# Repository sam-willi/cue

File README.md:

# Cue

**Speak with intention.** Cue is a discreet behind-the-ear (BTE) speech coach that gives a private haptic tap when a speaking habit (a run of fillers, rushing, no pauses, a long turn, speaking too quietly) is getting in your way, so you notice it in the moment and replace it with a pause.

This repository is the **software MVP**: a web app that listens through the microphone, detects these behaviors in real time, and shows each haptic cue on a 3D model of the device in place of the hardware. Product context, confirmed decisions, and open questions live in [`CUE_CONTEXT.md`](CUE_CONTEXT.md). Read it before proposing changes.

**Live demo:** https://cue-samanthajwilliamson-2541.vercel.app (it has no server Deepgram key, so use your own; see [Your own Deepgram key](#your-own-deepgram-key)).

> Status: prototype for validating the behavior loop. Not a medical device. Detection accuracy has not been measured on real users yet.

## How Cue decides to tap

Cue is a behavioral coach, not a filler counter ([`SOFTWARE.md`](SOFTWARE.md)). Detectors notice fillers, pace, pauses, turn length and volume; a **decision engine** (`src/lib/cue/engine.ts`) asks whether a tap would help right now. There are two modes, switched in the app or by double-tapping the device:

|                  | Conversation                              | Presentation                                                               |
| ---------------- | ----------------------------------------- | -------------------------------------------------------------------------- |
| Fillers          | 3 fillers within 12 s, or 8 per min       | um/uh above 5 per min over the last 60 s; "like"/"lowkey" count half       |
| Rushing          | 4.5 syl/s, then 20% over your own pace    | 4.0 syl/s, then 10% over your own pace                                     |
| No pause         | 30 s without a pause                      | 22 s without a ≥0.6 s pause                                                |
| Long turn        | 90 s                                      | Not live (a talk is one long turn)                                         |
| Too quiet        | 6 dB under your calibrated volume for 3 s | 6 dB under your calibrated volume for 10 s                                 |
| Gap between taps | 15 s cooldown (setting: 10–20 s)          | At least 25 s, at most 2 taps per minute; only the highest priority taps\* |

\* Presentation priority when several are due at once: rushing > no pause > filler > too quiet. The Presentation numbers are research-based starting points to test ([`CUE_CONTEXT.md`](CUE_CONTEXT.md) §26, decision 11).

- **Patterns, not single fillers.** One "um" is normal. Settings has an "every filler" testing mode (cooldown drops to 1.5 s). Whether patterns or every filler helps more is still a working assumption to test.
- **Pace against your own normal.** Rushing starts at the preset and, after your first minute of speech, becomes 20% (Conversation) or 10% (Presentation) over your own pace, never below 3.6 syl/s and never above 6 syl/s (about 250 words a minute), so a session that opens with very fast talking can't teach Cue that it is normal. A pace just over the limit has to hold for 3 s; at 1.25 times the limit or more, 1.5 s is enough.
- **Sustained behaviors wait for a natural break** (up to 3 s; 1 s for rushing, since someone racing ahead rarely leaves one) so the tap doesn't land mid-word.
- **Did it work?** 8 s after each tap Cue checks whether you paused, slowed down, stopped the fillers or spoke up, and gives more room next time if you did. Review shows "tapped: 3 in 9 s, and it worked".

## What it detects

| Behavior                              | How                                                                                                                                                                                                                                                                                                                                                                                                                                                                                                                                                                                                                                                                                                                                                                                                                                                              |
| ------------------------------------- | ---------------------------------------------------------------------------------------------------------------------------------------------------------------------------------------------------------------------------------------------------------------------------------------------------------------------------------------------------------------------------------------------------------------------------------------------------------------------------------------------------------------------------------------------------------------------------------------------------------------------------------------------------------------------------------------------------------------------------------------------------------------------------------------------------------------------------------------------------------------- |
| "um", "uh" (also "er", "erm", "ah")   | Deepgram **Flux** streaming ASR (results every ~0.2 s, keeps fillers; Nova-3 drops most fillers live). "hmm" is not counted: it's often a listening sound.                                                                                                                                                                                                                                                                                                                                                                                                                                                                                                                                                                                                                                                                                                       |
| Filler "like"                         | Rules over neighbouring words, part-of-speech tags, punctuation and pauses. "I like went to the mall" counts; "I like tofu" doesn't. Ambiguous cases never count, and every decision has a readable reason.                                                                                                                                                                                                                                                                                                                                                                                                                                                                                                                                                                                                                                                      |
| Quote "like" ("she was like, no way") | On by default, toggle in Settings                                                                                                                                                                                                                                                                                                                                                                                                                                                                                                                                                                                                                                                                                                                                                                                                                                |
| "About" "like" ("like twenty people") | Off by default, toggle in Settings                                                                                                                                                                                                                                                                                                                                                                                                                                                                                                                                                                                                                                                                                                                                                                                                                               |
| Filler "lowkey"                       | Its own classifier (`lowkeyClassifier.ts`): "it's lowkey good" counts; "keep it low-key" doesn't.                                                                                                                                                                                                                                                                                                                                                                                                                                                                                                                                                                                                                                                                                                                                                                |
| Speaking too fast                     | Syllables per second over a rolling 8 s window, pauses over 0.6 s excluded, sustained for 3 s. Thresholds above.                                                                                                                                                                                                                                                                                                                                                                                                                                                                                                                                                                                                                                                                                                                                                 |
| No pause                              | Time since your last meaningful pause. A pause is a gap of 0.6 s or more between your words, or the same length of real silence in the mic audio (Silero voice detection, `src/lib/audio/voiceDetector.ts`): word timings from the transcript drift, so either counts. If the voice detector can't load, word timing is used alone.                                                                                                                                                                                                                                                                                                                                                                                                                                                                                                                              |
| Long turn                             | How long your current speaking turn has run ("give the other person space"). Conversation only.                                                                                                                                                                                                                                                                                                                                                                                                                                                                                                                                                                                                                                                                                                                                                                  |
| Speaking too quietly (calibrated)     | You set the target with a short read-aloud (**Set my volume**) for each mode, saved on this device only as one loudness number per mode (no audio). Mic level is K-weighted (the ITU-R BS.1770 filter, so low rumble doesn't count) and measured only while you're actually voicing a word: inside a word's time span from the transcript, and where the voice detector heard a voice (the "active speech level" idea from ITU-T P.56). It is and adjusted for room noise (0.6 dB per dB of noise change, capped at ±10 dB). Without a calibration for the current mode, too-quiet cues are off and the app asks you to set it. A **Volume feedback** switch per mode turns volume coaching off entirely, so you never have to set a volume for that mode (saved on this device). Gain control and noise suppression are off so the measurement isn't distorted. |

"um"/"uh" are detected on the first confident result (confidence ≥ 0.8), and a clear filler "like" as soon as the next word is heard; ambiguous cases wait for more words. Detection is not the same as a tap: taps follow the pattern rules above. Each cue's measured delay appears in the app.

### Three cues

Live, Cue only ever asks for three things (decision 18). Every cue starts with a sharp onset (`src/lib/cue/patterns.ts`).

| Cue       | Haptic                                         | When                                                        |
| --------- | ---------------------------------------------- | ----------------------------------------------------------- |
| Pause     | One tap (50 ms)                                | No pause for a while, a long turn, or a run of filler words |
| Slow down | Slow steps (three 100 ms pulses, 250 ms apart) | Rushing                                                     |
| Speak up  | Long push (450 ms)                             | Too quiet                                                   |

On screen, each cue appears as a large card right under the controls, in its color (pause red, slow down orange, speak up green, matching the report), with what to do and why. It stays six seconds, long enough to glance down and read, and every cue so far is listed under it with the time it came. The 3D device at the bottom of the page still draws each cue as rings leaving the motor; a faint gray ring there means "noticed, not a pattern yet", a testing aid.

**Your own filler words.** In Settings you can add up to 20 words or short phrases you lean on ("so", "basically", "you know"). Cue counts one every time it's said (there's no check of how it was used, unlike "like"), and they feed the same pattern rules as the built-in fillers. The list is saved on this device. The list is also sent to Deepgram as "keyterms", words to listen for specially, so they are transcribed more reliably.

### Session report

When a session ends, the app builds a report (decision 19, `src/lib/cue/report.ts`, drawn by `src/app/ReportView.tsx`): a **Speak score**, directly under it **what to do differently next time**, then one card per area.

**Next time, do this.** Up to three actions, the one that cost the most points first. Each is an action in a few words ("Slow down"), how in one sentence ("Finish the last word of each sentence, breathe in, then begin the next one"), and the finding behind it ("Pace: you were rushing 23% of the time"). The full technique with its drill is on that area's card.

**Speak score (decision 25).** One number out of 100 with a level (Very low, Low, OK, High, Very high), built from points per area the way a sleep score is: pace 30, pauses 25, filler words 25, volume 10, pitch 10. Each area earns points on a sliding scale, not pass or fail. An area that couldn't be measured (no microphone, no volume set) is left out and the rest are scaled to 100. Fillers at or under two a minute earn full points, so it is not a test of saying none. It needs about 30 seconds of talking. Reading from notes and wording are not scored.

**Graphics.** Pace is a line over the comfortable range with any rushing picked out; pauses are a strip of the session where each bar is a stretch of talking and each gap a pause; pitch is a contour around your typical pitch; fillers are bars; volume and reading from notes are meters with the line worth working on marked. **Color (decision 26).** Each scored area has its own vivid color wherever it appears (its ring segment, icon, chart and technique), in rainbow order round the ring: pauses red, pace orange, volume green, filler words blue, pitch violet. Colors are used at full strength on gray, with no pale washes. Color says which area, never good or bad. The part worth working on is drawn in ink, so it stands apart from every hue for any kind of color vision. The colors are tokens in `globals.css` (`--area-*`), with brighter steps for dark mode. Each area has a **technique** (decision 24): one physical action plus a drill, such as "Land the last word" for rushing. Its one-sentence form is what "Next time, do this" shows; the full version with the drill is on every card, open where the area needs work and one press away otherwise, so it can be read even when a session flagged nothing. It appears under **Speaking insights**. The button of the same name beside Start listening opens it and scrolls to it; while a session is running the button reads "Stop and see insights" and ends the session first.

| Area               | What it reports                                                                                                                                                                                               |
| ------------------ | ------------------------------------------------------------------------------------------------------------------------------------------------------------------------------------------------------------- |
| Pauses             | How often you paused and your longest stretch without one.                                                                                                                                                    |
| Pace               | Average and fastest words per minute, the share of the session spent rushing, a chart of pace from start to finish, and what you were saying where you sped up: up to three quoted passages with their times. |
| Volume             | How much of the session you spent well below the volume you set (needs a set volume).                                                                                                                         |
| Filler words       | Fillers per minute and a count of each word, including your own. If you leaned on a common habit word that isn't on your list ("basically", "you know"), the report offers to add it.                         |
| Pitch and tone     | How much your pitch moved, from the microphone (`src/lib/cue/pitch.ts`, using the pitchy library). Under 2 semitones of spread reads as flat.                                                                 |
| Reading from notes | If you paste your notes or script, the share of your talk that matched them word for word (runs of 5+ words). Notes stay in the browser tab.                                                                  |
| Inclusive language | Terms from a list of about 570 (`src/lib/cue/inclusive.ts`), each with an alternative. Most come from retext-equality, cut down to what suits speech by `scripts/build-inclusive.mjs`.                        |

Pitch and volume need a microphone session. All of the report's thresholds are starting points that haven't been tested with users yet.

**Touch controls (simulated in the app).** The device's touch surface is for controls only: **hold 1.5 s** = Cue on/off, **double-tap** = switch Conversation / Presentation mode. A single tap or a lingering touch does nothing, so adjusting your hair or glasses won't trigger it. Confirmations are swelling or fading _ramps_ with no sharp onset, drawn as a neutral glow without rings, so they can't be mistaken for a coaching cue.

**Only the wearer is coached, by hardware.** On the device, a bone-conduction sensor confirms when you're the one speaking; the microphone (which hears everyone) feeds speech-to-text; a vibration motor behind the ear taps. Cue coaches only words the bone sensor confirms. This web prototype has no bone sensor, so it treats all speech as yours; Practice can simulate a friend cutting in.

A detection is withheld (not tapped) when confidence is too low, when it isn't a pattern yet, within the gap after the last tap, while muted, when its category is off, or when the behavior isn't live in the current mode. Withheld detections still show in the app's "Why Cue acted" log.

### Continuous learning

Cue learns each wearer across sessions and changes how it coaches them (decision 27, [`docs/continuous-learning.md`](docs/continuous-learning.md)): **observe** (a digest of numbers after each session) → **discover** (patterns that hold across sessions) → **remember** (a profile in this browser) → **adapt** (a personal coaching plan the live engine uses) → **evaluate** (taps against taps held back on purpose, strategies against each other) → **improve** (adopt what works, step back where you've improved, move your focus on).

- **Your focus** under the controls: one skill at a time, picked from your sessions or by you.
- **Cue updated** cards after a session, only when Cue learned or changed something, with "That's not right" to undo it.
- **A check-in** after each session: were the taps helpful, too many, or distracting, and what kind of session it was.
- **What Cue has learned**: your speaking patterns, your preferences, and how Cue has adapted (what it learned, what it changed), with controls to confirm, correct, pause, forget a session, or reset.
- **Learning timeline**: how you've improved, and how Cue has improved at coaching you.
- **Practice sandbox**: a separate memory for practice sentences and simulated speakers, so they never teach Cue about your real speech.

## Testing with AirPods

Until the device exists, AirPods (or any headphones with a mic) can stand in for it in user tests. This is a testing
stand-in, not the product: Cue stays one behind-the-ear device that taps.

1. Connect the AirPods, open the app, and switch on **Cue sounds in AirPods**. Each cue then also plays as a quiet sound
   in the ear, with the same rhythm as its tap and one pitch per family (Space high, Pace middle, Voice low).
   Confirmations swell in softly so they never sound like a cue. Volume and a test sound are in **Settings → Testing
   with AirPods**.
2. On a laptop, pick the AirPods under **Settings → Microphone**. On iPhone, connected AirPods are used automatically.
   While listening, the app shows which mic it's using.
3. **Set my volume** again with the AirPods in. Volume targets are saved per microphone, because the AirPods mic hears
   you at a different level from a laptop or phone mic.
4. Keep the page open while you talk: the screen stays on while listening, because a locked phone stops the mic.

Limits: the AirPods mic still picks up other people (more quietly), so their fillers can tap too; Bluetooth adds a
little delay to each sound; on iPhone, test with the ring switch both ways the first time.

## Quick start

Requires Node 24 (see `.nvmrc`). A Deepgram key on the server is optional.

```bash
npm install
cp .env.local.example .env.local   # optional: paste a Deepgram key
npm run dev
```

Open http://localhost:3000.

- **Try a sentence** plays typed text through the same detectors. It doesn't need a key.
- **Start listening** streams your mic to Deepgram for live detection, using the server's `DEEPGRAM_API_KEY` if it has one (the key needs the **Member** role or higher to mint browser tokens) or your own key.
- **Mark mistakes**: click a word in the transcript, or use the buttons in "Why Cue acted", to flag a wrong tap or a missed filler.
- **Download session** (after a live session) saves the words and timings Deepgram heard, your corrections, cue delays, your settings and mic loudness levels (no audio). Put the files in `sessions/` and run `npm run eval`.
- **Training** (only under `npm run dev`; hidden on deployed sites) records a labeled session to `training/` on your machine. See [CONTRIBUTING.md](CONTRIBUTING.md).

### Your own Deepgram key

**Use your own Deepgram key** is always available, and when set it overrides the server's key. The key is kept in this browser only: `sessionStorage` (this tab), or `localStorage` if you tick **Remember on this device**. The browser connects straight to Deepgram with the key as a WebSocket `token` subprotocol; it never passes through Cue's server. If Deepgram rejects the key, the form reopens. Without a server key and without your own, **Start listening** opens the form (the token route answers 503).

## Landing pages

Five pages for a painted-door test, one per market, at `/for/<market>`: `speaking`, `sales`, `schools`, `english` and `interviews`. They share one layout (`src/app/for/[market]/page.tsx`) and differ only in copy (`src/lib/landing/markets.ts`). Search engines are asked not to index them, so visits come from ads.

The photos are panels cut from one product concept sheet, [`assets/product/cue-concept-sheet.webp`](assets/product/cue-concept-sheet.webp), by `node scripts/landing-images.mjs`, which writes them to `public/landing/`. The sheet is the owner's image and is kept in the repo so other pages and materials can use it.

Each page has a sign-up form. A sign-up records the market, the email, and the `utm_source`, `utm_medium`, `utm_campaign`, `utm_content` and `utm_term` tags on the page address, so tag each ad's link (`/for/sales?utm_source=meta&utm_campaign=sales-a`). The schools page asks for a pilot; the school is an optional field, so an email alone is enough. On every page the email field and button come first in the form, so they show on a phone without scrolling.

**Where sign-ups go.** A Google Sheet with one tab per landing page (Speaking, Sales, Schools, English learners, Interviews), through a small script that lives in the sheet:

1. Create a Google Sheet. Open **Extensions → Apps Script**, replace the editor's contents with [`scripts/signups-sheet.gs`](scripts/signups-sheet.gs), and save.
2. Optional: choose `setup` in the editor's function menu and press **Run** to create the five tabs now. Otherwise each tab appears when its page gets its first sign-up.
3. **Deploy → New deployment → Web app**. Set **Execute as** to _Me_ and **Who has access** to _Anyone_, deploy, and approve the access prompt. Copy the web app URL (it ends in `/exec`).
4. In Vercel, add that URL as the environment variable `SIGNUPS_SHEET_URL` (Project → Settings → Environment Variables), then redeploy.

Each sign-up is added as a row on its page's tab within a second or two of the visitor pressing the button. A sign-up from a page the script doesn't list goes to a tab called Other, so add new pages to `TABS` at the top of the script. Anyone with the URL can add rows, so treat it like a password: it stays in Vercel and is never sent to the browser. If you change the script later, publish it with **Deploy → Manage deployments → Edit → New version** so the URL stays the same.

Without `SIGNUPS_SHEET_URL`, `npm run dev` saves sign-ups to `./signups/signups.jsonl` (git-ignored), and a deployed site tells the visitor it couldn't save and keeps nothing.

**Counting visits.** The landing pages load [Vercel Web Analytics](https://vercel.com/docs/analytics) (`<Analytics />` in `src/app/for/[market]/page.tsx`), so the project's **Analytics** tab in Vercel shows visitors and page views per page. Turn it on once under Project → Analytics → Enable. It uses no cookies, counts nothing under `npm run dev`, and is not loaded on the coaching app at `/`. Compare each page's visitors with the rows on its tab in the sheet to get a sign-up rate.

**Counting form use.** The sign-up form sends four custom events to Web Analytics, each with only the market: `signup_start` (the email box was focused, once per visit), `signup_submit` (the button was pressed), `signup_done` (the sign-up was saved) and `signup_failed`. Together with visits they show where people drop off: never starting, starting and not sending, or sending and failing. They appear under **Events** in the project's Analytics tab.

## Preorder page

`/preorder` sells batch 1: a $20 refundable deposit today on a $110 preorder with Premium free for life, the $90 balance charged when the batch ships (500 units, summer 2027). The offer lives in [`src/lib/preorder/offer.ts`](src/lib/preorder/offer.ts), so the page, checkout and tests agree; change it there.

- **Images.** Every product shot comes from two studio renders of the three colorways side by side: [`assets/product/cue-colorways-renders.webp`](assets/product/cue-colorways-renders.webp) (three-quarter view) and [`assets/product/cue-colorways-side.webp`](assets/product/cue-colorways-side.webp) (side view). `node scripts/colorway-cutouts.mjs` lifts each product onto a transparent background with the subject cut-out built into macOS (`scripts/cutout.swift`, macOS 14 or later) and writes `<color>-render.webp` and `<color>-side.webp` to `public/preorder/cutout/`. Replace a sheet (same layout: one colorway per third) and run it again on a Mac.
- **Deposits.** With `STRIPE_SECRET_KEY` set in Vercel, "continue to payment" opens Stripe Checkout for the deposit and saves the card for the balance. Each payment is tagged `cue_preorder=batch-1` and its colorway, and the page counts tagged payments (refreshed about once a minute) to show places left. Stripe sends buyers back to `/preorder/reserved`. Refunds and charging the balance are done in the Stripe dashboard for now.
- **Demo.** `/preorder/try` is the voice demo on its own page, opened in a new tab from the header ("try the demo") and from the cue section. It runs the coaching engine on the visitor's microphone for 45 seconds through `/api/deepgram-token`, so it needs `DEEPGRAM_API_KEY`; without it, the page says the demo is resting.
- **Link preview.** `node scripts/preorder-social.mjs` renders `public/preorder/social.png` and a 3-second loop of the tap, `public/preorder/social.mp4` (needs ffmpeg). Run it again after changing the headline or the cut-outs.
- **Without Stripe.** The dialog says deposits open soon and holds the price by email. Reservations go to the sign-up sheet (see Landing pages) on a **Preorder** tab with the colorway; paste the updated [`scripts/signups-sheet.gs`](scripts/signups-sheet.gs) and publish a new version to get that tab and column.

## Scripts

| Command                           | What it does                                                                                                                                                                                                                                       |
| --------------------------------- | -------------------------------------------------------------------------------------------------------------------------------------------------------------------------------------------------------------------------------------------------- |
| `npm run dev`                     | Dev server (also the only place the Training section appears)                                                                                                                                                                                      |
| `npm test`                        | Unit tests (Vitest)                                                                                                                                                                                                                                |
| `npm run test:watch`              | Unit tests in watch mode                                                                                                                                                                                                                           |
| `npm run eval`                    | Replay saved sessions and labeled training recordings; report fillers caught / missed / wrong                                                                                                                                                      |
| `npm run lint`                    | ESLint                                                                                                                                                                                                                                             |
| `npm run typecheck`               | Route type generation and `tsc --noEmit`                                                                                                                                                                                                           |
| `npm run format:check`            | Prettier check                                                                                                                                                                                                                                     |
| `npm run check`                   | Lint, typecheck, format check and tests, the same as CI                                                                                                                                                                                            |
| `npm run format`                  | Format with Prettier                                                                                                                                                                                                                               |
| `npm run build`                   | Production build. Like `npm run dev`, it first copies the voice detector's runtime and model into `public/vad/` (`scripts/copy-vad-assets.mjs`)                                                                                                    |
| `npm run cad`                     | Rebuild the 3D device (`public/cad/cue-bte.glb`) after the CAD changes. Accepts a zoo.dev GLB or STEP (`npm run cad -- in.glb`); by default reads `origin/hardware-rev0:hardware/rev0/democad.step`, so run `git fetch origin hardware-rev0` first |
| `python3 scripts/brand-assets.py` | Regenerate the interim logo and favicon rasters in `public/brand/` (needs Pillow and numpy)                                                                                                                                                        |

## How it works

```text
mic ──AudioWorklet (16 kHz PCM)──▶ Deepgram Flux (v2/listen, flux-general-en)
                                           │ timed words (updates every ~0.2 s)
                                           ▼
                                   parse (src/lib/deepgram/parse.ts)
                                           ▼
       CueSession: bone gate (wearer's words only) ─▶ detectors
         um/uh · like · lowkey · your words · pace · no pause · long turn · too quiet
                                           ▼
       DecisionEngine: pattern? confident? mode? gap since last tap? natural break?
                                           ▼
                                  haptic pattern (three cues)
```

| Path                                  | Role                                                                                        |
| ------------------------------------- | ------------------------------------------------------------------------------------------- |
| `src/lib/cue/session.ts`              | Consumes streaming words, applies the bone gate, runs the detectors                         |
| `src/lib/cue/engine.ts`               | The decision engine: patterns, modes, gaps between taps, natural breaks, did-it-work checks |
| `src/lib/cue/likeClassifier.ts`       | Decides how each "like" is used (filler, quote, approximation, verb, comparison, …)         |
| `src/lib/cue/lowkeyClassifier.ts`     | Decides whether "lowkey" is a filler                                                        |
| `src/lib/cue/pace.ts`, `syllables.ts` | Rolling speaking rate                                                                       |
| `src/lib/cue/loudness.ts`             | Speech loudness, room noise and the too-quiet check                                         |
| `src/lib/cue/patterns.ts`             | The five haptic cues and the touch-control ramps                                            |
| `src/lib/cue/touch.ts`                | Touch gestures (hold = on/off, double-tap = mode)                                           |
| `src/lib/cue/evaluate.ts`             | Scores saved sessions and training recordings for `npm run eval`                            |
| `src/lib/cue/config.ts`               | Defaults and mode presets                                                                   |
| `src/lib/cue/plan.ts`                 | The personal coaching plan the live engine reads (from continuous learning)                 |
| `src/lib/learning/`                   | Continuous learning: digest, patterns, evaluation, plan, focus, the learning loop, storage  |
| `src/app/learning/`                   | Your focus, Cue updated, the check-in, What Cue has learned, the learning timeline          |
| `src/lib/deepgram/liveTranscriber.ts` | Mic capture and Deepgram WebSocket client                                                   |
| `public/pcm-worklet.js`               | AudioWorklet that turns mic audio into 16 kHz PCM                                           |
| `src/app/api/deepgram-token/route.ts` | Mints 30 s Deepgram tokens from the server's key; 503 when the server has none              |
| `src/app/api/training/route.ts`       | Saves training recordings to `training/` (local development only)                           |
| `src/app/CueApp.tsx`                  | The UI                                                                                      |
| `src/app/DeviceModel.tsx`             | The 3D device, with haptics drawn as rings from the motor                                   |
| `scripts/cad-to-glb.mjs`              | Converts the device CAD (zoo.dev GLB or STEP) into `public/cad/cue-bte.glb`                 |
| `scripts/brand-assets.py`             | Builds the interim logo rasters from the approved concept                                   |

## Open-source pieces

| Piece                                                                                                                         | Used for                                                                                               | License   |
| ----------------------------------------------------------------------------------------------------------------------------- | ------------------------------------------------------------------------------------------------------ | --------- |
| [Silero VAD](https://github.com/snakers4/silero-vad) model, shipped by [@ricky0123/vad-web](https://github.com/ricky0123/vad) | Hearing real pauses in the mic audio                                                                   | MIT / ISC |
| [onnxruntime-web](https://github.com/microsoft/onnxruntime)                                                                   | Running that model in the browser (about 14 MB, fetched from this site when listening starts)          | MIT       |
| [libebur128](https://github.com/jiixyj/libebur128) and [pyloudnorm](https://github.com/csteinmetz1/pyloudnorm)                | Reference for the K-weighting formulas in `src/lib/cue/loudness.ts` (no code copied, not a dependency) | MIT       |
| [pitchy](https://github.com/ianprime0509/pitchy)                                                                              | Voice pitch for the report                                                                             | 0BSD      |
| [retext-equality](https://github.com/retextjs/retext-equality)                                                                | Source of most of the inclusive-language list (build time only)                                        | MIT       |
| [compromise](https://github.com/spencermountain/compromise)                                                                   | Part-of-speech tags for the "like" rules                                                               | MIT       |

## Privacy

Live mode sends microphone audio to Deepgram for transcription. This is a disclosed exception for the MVP; the product is meant to move to on-device or phone-local recognition before launch ([`CUE_CONTEXT.md`](CUE_CONTEXT.md) §26, decision 9). The coaching app stores nothing on a server: no audio, transcripts, or events leave the browser tab except as an explicit **Download session** file. The landing pages are separate: a sign-up sends the email address, market and ad tags to the sign-up sheet, and each visit is counted by Vercel Web Analytics without cookies (see Landing pages). What stays in your browser: your own Deepgram key if you entered one (see above), one volume number per mode if you calibrated, and what Cue has learned about how you speak (numbers from each session, your filler words and a few phrases you repeat, your preferences; never audio or transcripts), which you can pause, correct, or reset in **What Cue has learned**. **Training recordings** are opt-in, only possible under `npm run dev`, and are written to `./training/` on your machine (git-ignored). Don't commit session files or training recordings; they contain transcripts and audio.

## Contributing

See [CONTRIBUTING.md](CONTRIBUTING.md). Report security issues privately as described in [SECURITY.md](SECURITY.md).

## License

Proprietary. All rights reserved. See [LICENSE](LICENSE).

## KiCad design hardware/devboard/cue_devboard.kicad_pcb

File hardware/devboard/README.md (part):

# Cue rev A dev board

A 33 × 21 mm, 4-layer board (signal / GND / 1V8 / signal) with the cuff circuits plus bench conveniences: USB-C
charging, JST-PH battery and JST-SH motor connectors, SWD debug and back-side test pads (TP1–TP13) for probing.

**Radio module: Ezurio BL54L15 453-00044** (14 × 10 mm, MHF4 antenna connector). The cuff's BL54L15µ (453-00223) is
out of stock everywhere until about Dec 2026, so the dev board uses its bigger sibling. Same nRF54L15 chip and the
same port pins as the cuff, so firmware is identical. It needs a plug-in 2.4 GHz antenna (see below).

**Status: ready to order (2026-10-08).** Big A re-laid the board out at 33 × 21 mm (from 42 × 32). Checked: DRC 0
unconnected / 0 schematic-parity issues / no copper clearance, short or hole errors (nothing under the 0.127 mm rule);
schematic = `devboard_circuit.py` = PCB pad for pad; every pin map and footprint checked against the manufacturers'
datasheets. Remaining DRC warnings are accepted: courtyard overlaps, small silkscreen text, single-spoke thermals, J2
mounting pads 0.2 mm from the edge. The schematic and PCB are now hand-edited in KiCad 10: `make_schematic.py` and
`build_board.py` reproduce the older 42 × 32 board only.

Changes in the 33 × 21 board:

- J5 expansion header removed; PDM_CLK, PDM_DIN and EXP_P0_01 moved to test pads TP11–TP13 (back side).
- BUCK2 removed (the 3.0 V rail only fed J5): L2, C7, R4, TP5 gone; SW2 open, VSET2 to GND (off at start-up),
  VOUT2 to VSYS, per nPM1300 PS Configuration 2 (Fig. 57).
- U3 pin 9 (AH2/QVAR2) tied to GND: ST DS13771 Table 2 says never leave it floating.
- J1 shield pads are "SH" (KiCad 10 footprint) and on GND. Fiducials removed (JLCPCB adds them on the edge rails).

Open before or at order:

- J4: an Arm-style debug cable with position 7 plugged needs pin 7 missing on the header. The keyed header is in
  stock at JLCPCB as FTSH-105-01-L-DV-**007**-K-P-TR, **C5885449** (959 on 2026-10-11): swap it into `bom.csv`, or
  pull pin 7. The cable on the parts list (Samtec FFSD-05-D-02.00-01-N) is keyed on its housing instead, so check
  whether it has position 7 open before deciding.
- Radio keep-out: a 1V8 via at (71.8, 93.3) and the end of PMIC_INT (B.Cu, ~0.8 mm) sit under the BL54L15's RF end.
  Low risk with the MHF4 module (ground pour is allowed there); move them on the next spin.
- C2 (extra 10 µF on VBUS, 11 µF total vs the USB 10 µF limit) and C4 (extra 1 µF on VSYS) are not in Nordic's
  reference; both are optional.
- **Wear sensing is not used** (decided 2026-10-11). Only U3's bone-conduction channel is used; its Qvar input,
  the E1 pad on the back and R6 are left unused. They stay on the board, so nothing changes in the order.

## Open it

Install KiCad (free, kicad.org) and open `cue_devboard.kicad_pro`. The schematic is `cue_devboard.kicad_sch`; the
board is `cue_devboard.kicad_pcb`. A PDF of the schematic is in `fab/schematic.pdf`.

## Order it (JLCPCB)

**Shopping list:** [`parts_list.xlsx`](parts_list.xlsx) has two tabs. **JLCPCB order** lists what comes on the
assembled board: every part, including both buttons, except the radio module. **Our order** lists what the team buys:
the radio module (soldered on by us), the antenna, battery, vibration motor and motor cable (plug in), and the tools
(probably at the IYA Makerspace).

**The order (decided 2026-10-11): 5 boards, all 5 assembled by JLCPCB, radio module fitted by the team.** Upload the
three files below: PCB quantity 5, PCBA quantity 5, top side, Standard PCBA. Buy the radio modules from Digi-Key
(one per board plus a spare) and solder them on when the boards arrive.

| File                           | Upload as                         |
| ------------------------------ | --------------------------------- |
| `fab/cue_devboard_gerbers.zip` | Gerber files (4 layers, 1.6 mm)   |
| `fab/bom.csv`                  | BOM (has an `LCSC Part #` column) |
| `fab/cpl.csv`                  | CPL / pick-and-place              |

Parts that need attention at order. **Stock check 2026-10-11:** every line of `bom.csv` was in stock in JLCPCB's parts library, including the power chip and the USB-C port that were out on 2026-10-05. Stock changes, so check again in the quote. Standard PCBA is needed.

| Ref      | Part                                               | Where                                                                                                                                                                                                                                                       |
| -------- | -------------------------------------------------- | ----------------------------------------------------------------------------------------------------------------------------------------------------------------------------------------------------------------------------------------------------------- |
| U1       | Ezurio BL54L15 **453-00044R** (radio module, MHF4) | **Not assembled by JLCPCB** (left out of `bom.csv` / `cpl.csv`). Buy from Digi-Key (sold singly: US$5.55, 1,328 in stock, 2026-10-11) and hand-solder; see below. JLCPCB lists it only as a pre-order part, C45868630 (no stock, US$12.51 each, 2026-10-11) |
| U2       | Nordic nPM1300-QEAA-R (power)                      | LCSC C7466043: in stock at JLCPCB (568 on 2026-10-11)                                                                                                                                                                                                       |
| SW1, SW2 | Omron (now Aratas) B3U-1000P buttons               | C231329: in stock at JLCPCB (128,809 on 2026-10-11). In `bom.csv` / `cpl.csv` since 2026-10-11                                                                                                                                                              |
| J1       | GCT USB4125-GF-A-0190 (USB-C)                      | C5246813: in stock at JLCPCB (3,213 on 2026-10-11)                                                                                                                                                                                                          |

**Hand-soldering U1:** the module has castellated pads on three edges only (none underneath), 0.75 mm pitch.
JLCPCB's stencil still pastes the U1 pads, so they arrive pre-tinned; if the module rocks, flatten them with wick. Align
the module with the silk outline (MHF4 connector at the top edge, next to the pin-1 dot), tack two opposite corners,
check alignment, then solder every pad with flux and a fine tip (or hot air). Check for bridges with a meter: VDD_nRF
(pad 26) to GND must not be shorted. Click the antenna on before powering the radio.

**JLCPCB BOM check (2026-10-05):** 22 of 23 BOM lines matched the intended LCSC numbers. U1 is left out of the JLCPCB order
(JLCPCB has no stock of it; buying from Digi-Key and hand-soldering is faster and cheaper). The PCBA quantity sets how many boards get populated: 5 of 5.

Also buy one **2.4 GHz antenna with an MHF4 plug** per board and click it onto the module (not assembled by JLCPCB).
Ezurio's approved list: mFlexPIFA **EFA2400A3S-10MH4L** (stick-on flex, recommended), FlexPIFA 001-0022, NanoBlue
EBL2400A1-10MH4L. Don't power the radio on without an antenna.
The wearable test mule uses the smaller Taoglas **FXP830.24.0100B** instead (42 × 7 mm, 100 mm of 0.81 mm cable, MHF4;
US$7.31 at Digi-Key). It is not on Ezurio's list, so it is for internal prototypes only: see `../enclosure/DESIGN.md`.

In JLCPCB's placement preview, check the rotation of U4, J1, J2, J3, SW1 and SW2 (each button's two pads must sit under its two end terminals) (`fab/placement_check.png` shows the
right answer): U4's port over the sound hole. When soldering U1 on, its MHF4 connector goes in the module's top-right
corner at the board's top edge, next to the pin-1 dot. Choose "edge rails added by JLCPCB" (connectors and the module sit at the board edges).

**Battery polarity:** J2 pin 1 is + (silk "+"). JST-PH battery leads are not standardised, so meter the cell's plug
before connecting: red (+) must land on the "+" pin.

Everything else has an LCSC number in `fab/bom.csv` (from `devboard_circuit.SOURCING`). The LSM6DSV16BX is in stock
under its second LCSC listing, C5267394 (the older C5381401 listing is dead).

LCSC-stocked alternatives, if you want everything sourced through JLCPCB (each needs a redesign):

| Instead of     | Alternative                                                    | LCSC                         | What changes                                                                                         |
| -------------- | -------------------------------------------------------------- | ---------------------------- | ---------------------------------------------------------------------------------------------------- |
| BL54L15 module | u-blox BMD-340 (nRF52840)                                      | C5456944 (19 in stock)       | New footprint and pin map, nRF52 firmware port, more current. No nRF54L15 module is stocked at LCSC. |
| nPM1300        | TI BQ25180 charger + TPS62840 1.8 V buck + TPS7A0230 3.0 V LDO | C3682423, C2071859, C3747031 | Three chips instead of one; new power section.                                                       |

## Design notes

- **Radio module** (BL54L15 453-00044, Ezurio BL54L10/BL54L15 datasheet): footprint from the host PCB land pattern
  (39 pads, 0.45 × 0.60 mm, 0.75 mm pitch). Module centred on the top edge with its RF / MHF4 end at the edge, inset
  0.1 mm for copper-to-edge clearance. No tracks or vias under the RF end (5 × 8.5 mm); ground pour is allowed, since
  this variant has no on-board antenna.
- **Pin map** (same nRF54L15 pins as the cuff): PDM_CLK P1.03 (pad 14), I2C_SCL P1.04 (23), TDM_BCLK P1.08 (30),
  I2C_SDA P1.13 (33), PDM_DIN P1.14 (32), TDM_DIN P1.06 (21), IMU_INT1 P1.07 (20), MIC_WAKE P1.05 (22),
  TDM_WCLK P1.11 (35, via R7), PMIC_INT P1.10 (28, via R8), MIC_THSEL P2.02 (8), HAPTIC_EN P2.00 (9),
  HAPTIC_TRIG P2.01 (10), BTN_USER P0.00 (17), EXP_P0_01 P0.01 (18). Clock signals are on pins the datasheet marks as
  clock pins.
- **R7, R8 (330 Ω)**: the cuff's BL54L15µ Note 7 needs them on P1.09–P1.12; the BL54L15 doesn't, but they stay so
  both boards behave the same.
- **nPM1300**: BUCK1 and the VSYS caps follow Nordic's PS v1.2.1 Configuration 1 (VSET1 47k = 1.8 V, 3 × 10 µF on
  VSYS); BUCK2 and LOADSW2 are unused and tied off per Configuration 2. 100 nF on VDDIO, 10k B3380 thermistor RT1 on NTC.
- **Mic safety**: the T5838 (1.98 V max) is behind load switch 1, which is off at reset.

- **Regulator layout** (nPM1300 PS 9.3.4 / Fig. 62–65): SW1/SW2 run 2.5 mm at 0.3 mm straight to L1/L2 with no vias,
  PVDD cap C5 1.5 mm from pin 4, output caps at the inductor outputs, 3 × 3 vias in the exposed pad. Other power
  traces are widened to 0.2–0.4 mm where clearance allows; keep the charge current at or below ~200 mA.

## Review (2026-10-05, second pass after the module change)

An independent review of the re-routed board found one must-check (battery polarity, now marked "+" / "-") and these,
all fixed: motor (LRA) lines ran beside PDM_CLK under the mic (J3 moved; now 2.1 mm away and 5 mm from the sound hole);
U2 exposed-pad vias sat inside the paste openings (now 4 vias in the gaps between them); vias touching the RT1, C6 and
C8 pads (moved off: `via_off_pads.py`); silkscreen below JLCPCB's 1.0 mm / 0.15 mm minimum (all text now 1.0 mm, test
points labelled on the bottom, button labels on top); L1 output now joins C6 directly on the top layer. U3 pin 7 (GND)
was isolated on one routing pass; it is now tied to C9's ground. Left as-is (fine at these currents): some
VSYS / VBAT / VBUS segments are 0.127 mm where the router had no room.

Checked against Ezurio's own CAD footprint (BL54L10/BL54L15 PCB footprint rev 4.0, May 2026: DXF, Altium PcbLib and
PDF): all 39 pads match in number, position and size (largest difference 0.003 mm, the left column at x = 0.503 vs
0.50 mm). Ezurio's files are not committed (their licence prohibits redistribution).

## Review (2026-10-05, first pass)

Every footprint and pin map was checked against the manufacturer's drawing (nPM1300, T5838 from the PDFs;
LSM6DSV16BX, DRV2605L, USB4125, FTSH-105, JST PH/SH, DFE201210U, B3U-1000P, ESD5Z, NCP15 from the web): no errors.
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
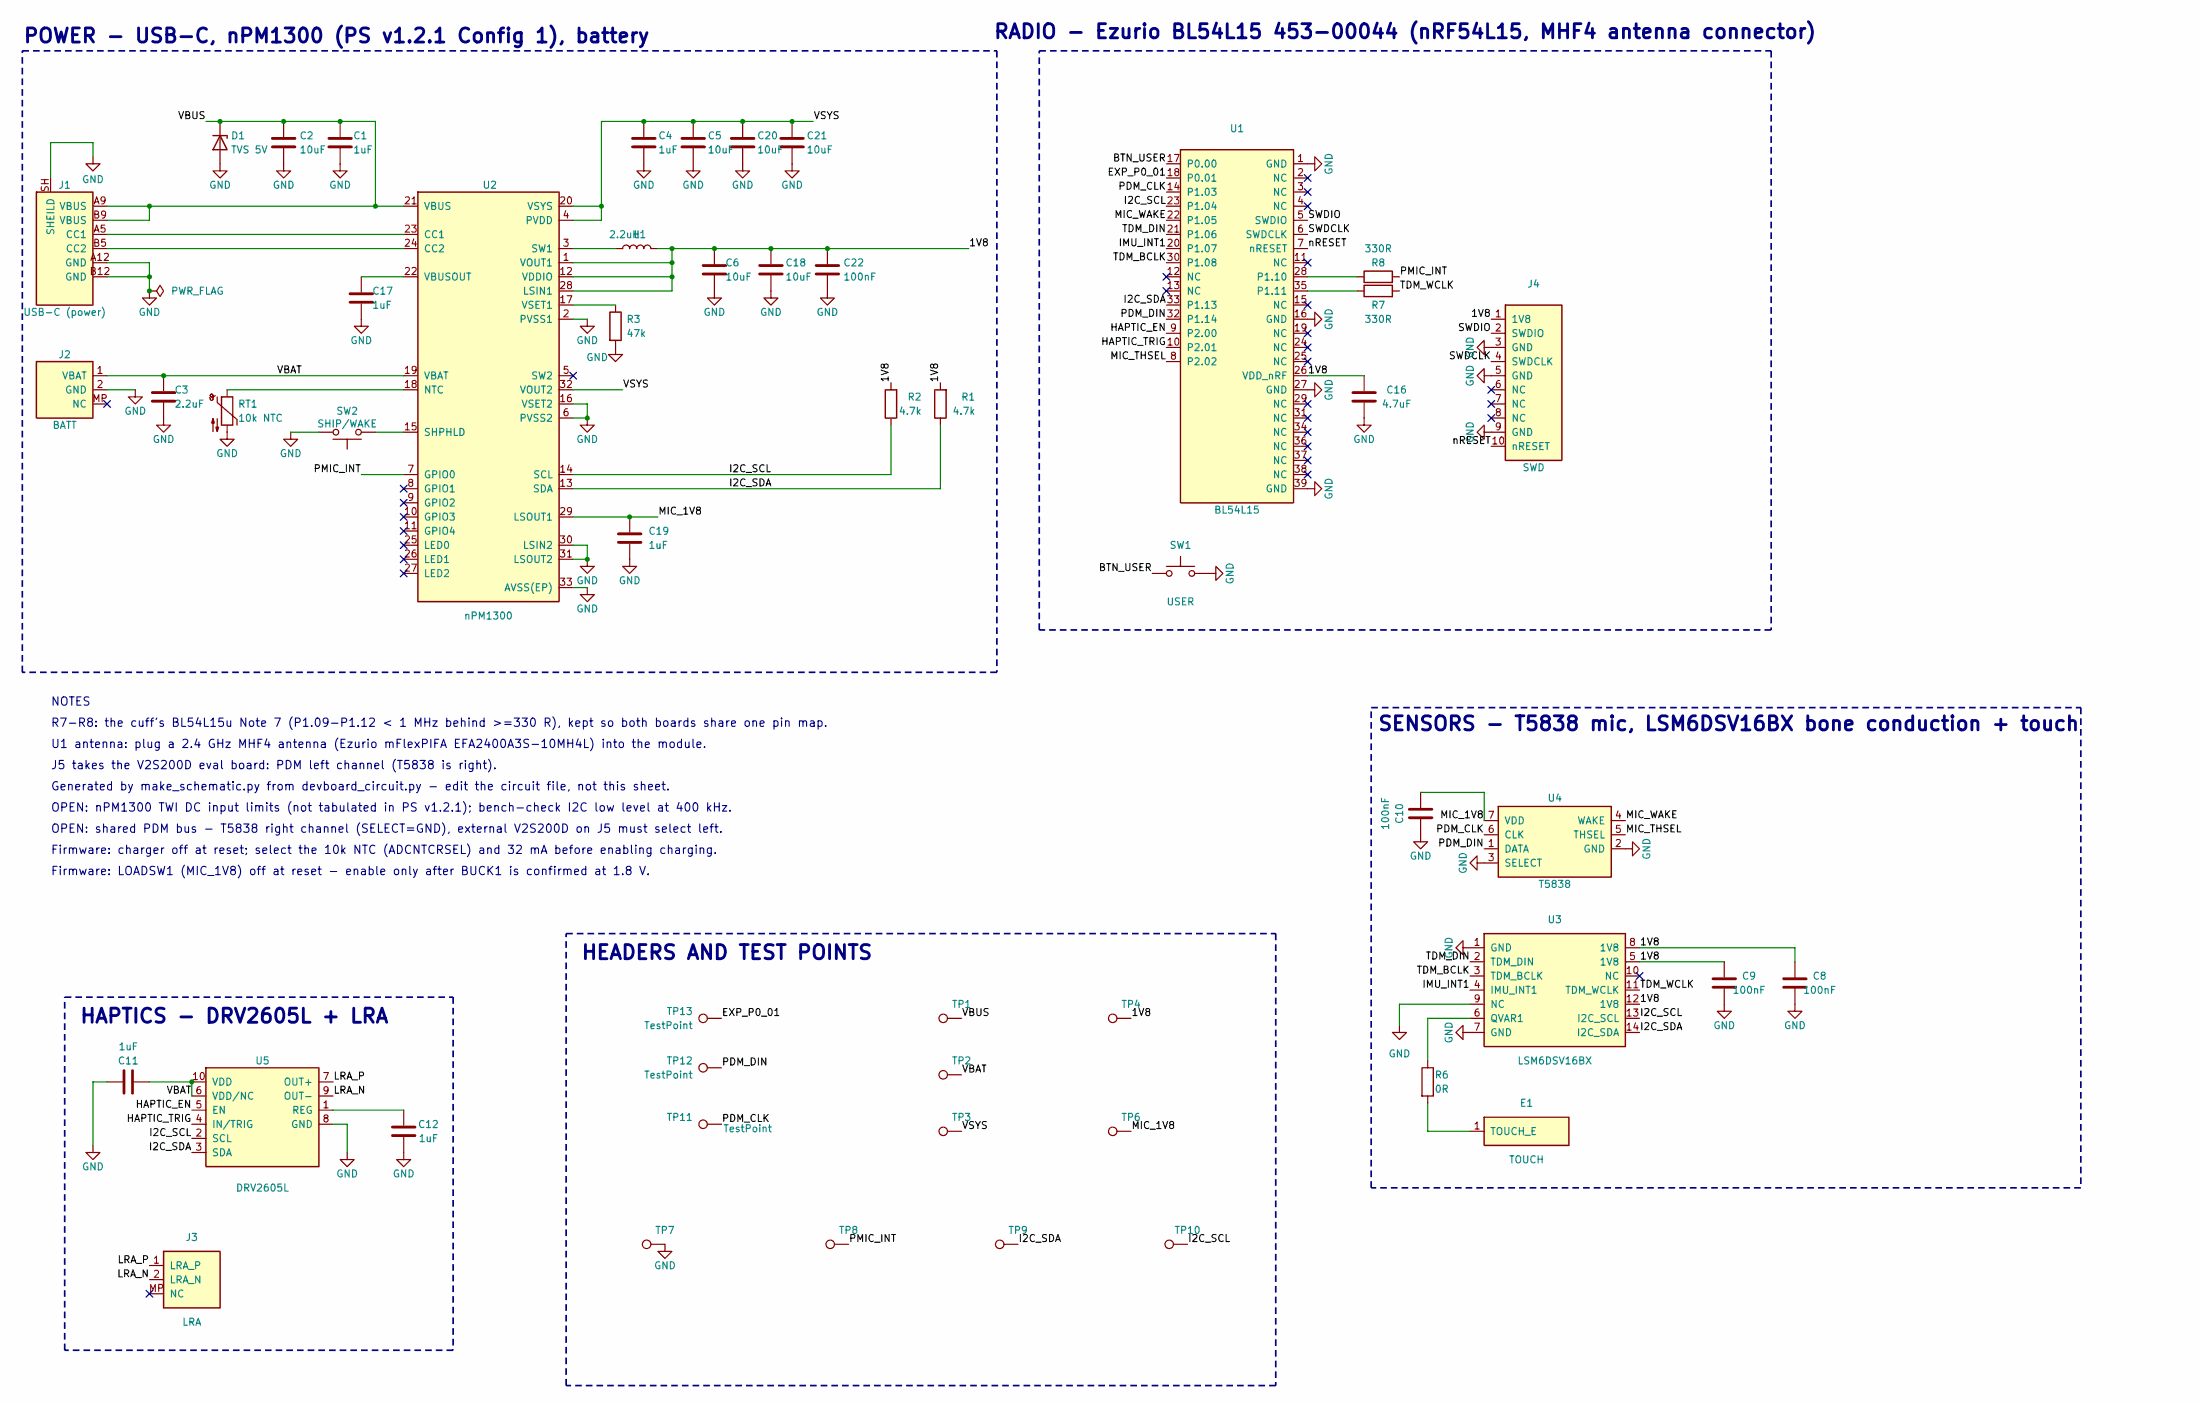
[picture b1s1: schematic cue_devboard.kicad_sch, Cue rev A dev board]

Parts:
C1, C4, C11, C12, C17, C19: 1uF; C_0402_1005Metric; MPN X5R/X7R ceramic, >=10 V
C2, C5, C6, C18, C20, C21: 10uF; C_0603_1608Metric; MPN X5R/X7R ceramic, >=10 V
C3: 2.2uF; C_0603_1608Metric; MPN X5R/X7R ceramic, >=10 V
C8, C9, C10, C22: 100nF; C_0402_1005Metric; MPN X5R/X7R ceramic, >=10 V
C16: 4.7uF; C_0402_1005Metric; MPN X5R/X7R ceramic, >=10 V
D1: TVS 5V; D_SOD-523; MPN onsemi ESD5Z5.0T1G
E1: TOUCH; Touch_Pad_4x3mm; MPN Copper pad (shell contact)
J1: USB-C (power); USB_C_Receptacle_GCT_USB4125-xx-x_6P_TopMnt_Horizontal; MPN GCT USB4125-GF-A
J2: BATT; JST_PH_S2B-PH-SM4-TB_1x02-1MP_P2.00mm_Horizontal; MPN JST S2B-PH-SM4-TB
J3: LRA; JST_SH_SM02B-SRSS-TB_1x02-1MP_P1.00mm_Horizontal; MPN JST SM02B-SRSS-TB
J4: SWD; PinHeader_2x05_P1.27mm_Vertical_SMD; MPN 2x5 1.27 mm SMD header
L1: 2.2uH; L_0805_2012Metric; MPN Murata DFE201210U-2R2M=P2
R1, R2: 4.7k; R_0402_1005Metric; MPN 1% thick film
R3: 47k; R_0402_1005Metric; MPN 1% thick film
R6: 0R; R_0402_1005Metric; MPN 1% thick film
R7, R8: 330R; R_0402_1005Metric; MPN 1% thick film
RT1: 10k NTC; R_0402_1005Metric; MPN Murata NCP15XH103F03RC
SW1: USER; SW_SPST_B3U-1000P; MPN Omron B3U-1000P
SW2: SHIP/WAKE; SW_SPST_B3U-1000P; MPN Omron B3U-1000P
TP1: TP VBUS; TestPoint_Pad_D1.0mm; MPN Test pad
TP2: TP VBAT; TestPoint_Pad_D1.0mm; MPN Test pad
TP3: TP VSYS; TestPoint_Pad_D1.0mm; MPN Test pad
TP4: TP 1V8; TestPoint_Pad_D1.0mm; MPN Test pad
TP6: TP MIC_1V8; TestPoint_Pad_D1.0mm; MPN Test pad
TP7: TP GND; TestPoint_Pad_D1.0mm; MPN Test pad
TP8: TP PMIC_INT; TestPoint_Pad_D1.0mm; MPN Test pad
TP9: TP I2C_SDA; TestPoint_Pad_D1.0mm; MPN Test pad
TP10: TP I2C_SCL; TestPoint_Pad_D1.0mm; MPN Test pad
TP11, TP12, TP13: TestPoint; TestPoint_Pad_D1.0mm
U1: BL54L15; Ezurio_BL54L15_453-00044; MPN Ezurio 453-00044
U2: nPM1300; QFN-32-1EP_5x5mm_P0.5mm_EP3.45x3.45mm; MPN Nordic NPM1300-QEAA-R
U3: LSM6DSV16BX; LGA-14_3x2.5mm_P0.5mm_LayoutBorder3x4y; MPN ST LSM6DSV16BXTR
U4: T5838; TDK_T5838; MPN TDK InvenSense T5838
U5: DRV2605L; VSSOP-10_3x3mm_P0.5mm; MPN TI DRV2605LDGSR

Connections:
/1V8: C6.1, C8.1, C9.1, C16.1, C18.1, C22.1, J4.1 (1V8), L1.2, R1.2, R2.2, TP4.1 (1_1), U1.26 (VDD_nRF), U2.1 (VOUT1), U2.12 (VDDIO), U2.28 (LSIN1), U3.5 (1V8), U3.8 (1V8), U3.12 (1V8)
/BTN_USER: SW1.1, U1.17 (P0.00)
/EXP_P0_01: TP13.1 (1_1), U1.18 (P0.01)
/HAPTIC_EN: U1.9 (P2.00), U5.5 (EN)
/HAPTIC_TRIG: U1.10 (P2.01), U5.4 (IN/TRIG)
/I2C_SCL: R2.1, TP10.1 (1_1), U1.23 (P1.04), U2.14 (SCL), U3.13 (I2C_SCL), U5.2 (SCL)
/I2C_SDA: R1.1, TP9.1 (1_1), U1.33 (P1.13), U2.13 (SDA), U3.14 (I2C_SDA), U5.3 (SDA)
/IMU_INT1: U1.20 (P1.07), U3.4 (IMU_INT1)
/LRA_N: J3.2 (LRA_N), U5.9 (OUT-)
/LRA_P: J3.1 (LRA_P), U5.7 (OUT+)
/MIC_1V8: C10.1, C19.1, TP6.1 (1_1), U2.29 (LSOUT1), U4.7 (VDD)
/MIC_THSEL: U1.8 (P2.02), U4.5 (THSEL)
/MIC_WAKE: U1.22 (P1.05), U4.4 (WAKE)
/PDM_CLK: TP11.1 (1_1), U1.14 (P1.03), U4.6 (CLK)
/PDM_DIN: TP12.1 (1_1), U1.32 (P1.14), U4.1 (DATA)
/PMIC_INT: R8.2, TP8.1 (1_1), U2.7 (GPIO0)
/SWDCLK: J4.4 (SWDCLK), U1.6 (SWDCLK)
/SWDIO: J4.2 (SWDIO), U1.5 (SWDIO)
/TDM_BCLK: U1.30 (P1.08), U3.3 (TDM_BCLK)
/TDM_DIN: U1.21 (P1.06), U3.2 (TDM_DIN)
/TDM_WCLK: R7.2, U3.11 (TDM_WCLK)
/VBAT: C3.1, C11.1, J2.1 (VBAT), TP2.1 (1_1), U2.19 (VBAT), U5.6 (VDD/NC), U5.10 (VDD)
/VBUS: C1.1, C2.1, D1.1 (K), J1.A9 (VBUS), J1.B9 (VBUS), TP1.1 (1_1), U2.21 (VBUS)
/VSYS: C4.1, C5.1, C20.1, C21.1, TP3.1 (1_1), U2.4 (PVDD), U2.20 (VSYS), U2.32 (VOUT2)
/nRESET: J4.10 (nRESET), U1.7 (nRESET)
GND: C1.2, C2.2, C3.2, C4.2, C5.2, C6.2, C8.2, C9.2, C10.2, C11.2, C12.2, C16.2, C17.2, C18.2, C19.2, C20.2, C21.2, C22.2, D1.2 (A), J1.A12 (GND), J1.B12 (GND), J1.SH (SHEILD), J2.2 (GND), J4.3 (GND), J4.5 (GND), J4.9 (GND), R3.2, RT1.2, SW1.2, SW2.2, TP7.1 (1_1), U1.1 (GND), U1.16 (GND), U1.27 (GND), U1.39 (GND), U2.2 (PVSS1), U2.6 (PVSS2), U2.16 (VSET2), U2.30 (LSIN2), U2.31 (LSOUT2), U2.33 (AVSS(EP)), U3.1 (GND), U3.7 (GND), U3.9 (NC), U4.2 (GND), U4.3 (SELECT), U5.8 (GND)
unnamed: E1.1 (TOUCH_E_1), R6.2
unnamed: J1.A5 (CC1), U2.23 (CC1)
unnamed: J1.B5 (CC2), U2.24 (CC2)
unnamed: R8.1, U1.28 (P1.10)
unnamed: R7.1, U1.35 (P1.11)
unnamed: RT1.1, U2.18 (NTC)
unnamed: SW2.1, U2.15 (SHPHLD)
unnamed: L1.1, U2.3 (SW1)
unnamed: C17.1, U2.22 (VBUSOUT)
unnamed: R3.1, U2.17 (VSET1)
unnamed: R6.1, U3.6 (QVAR1)
unnamed: C12.1, U5.1 (REG)

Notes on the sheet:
NOTES
Firmware: LOADSW1 (MIC_1V8) off at reset - enable only after BUCK1 is confirmed at 1.8 V.
Generated by make_schematic.py from devboard_circuit.py - edit the circuit file, not this sheet.
R7-R8: the cuff's BL54L15u Note 7 (P1.09-P1.12 < 1 MHz behind >=330 R), kept so both boards share one pin map.
SENSORS - T5838 mic, LSM6DSV16BX bone conduction + touch
Firmware: charger off at reset; select the 10k NTC (ADCNTCRSEL) and 32 mA before enabling charging.
J5 takes the V2S200D eval board: PDM left channel (T5838 is right).
HEADERS AND TEST POINTS
U1 antenna: plug a 2.4 GHz MHF4 antenna (Ezurio mFlexPIFA EFA2400A3S-10MH4L) into the module.
OPEN: nPM1300 TWI DC input limits (not tabulated in PS v1.2.1); bench-check I2C low level at 400 kHz.
OPEN: shared PDM bus - T5838 right channel (SELECT=GND), external V2S200D on J5 must select left.
RADIO - Ezurio BL54L15 453-00044 (nRF54L15, MHF4 antenna connector)
POWER - USB-C, nPM1300 (PS v1.2.1 Config 1), battery
HAPTICS - DRV2605L + LRA

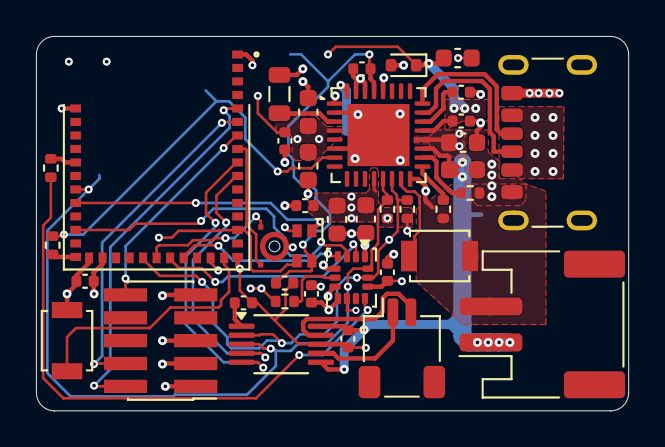
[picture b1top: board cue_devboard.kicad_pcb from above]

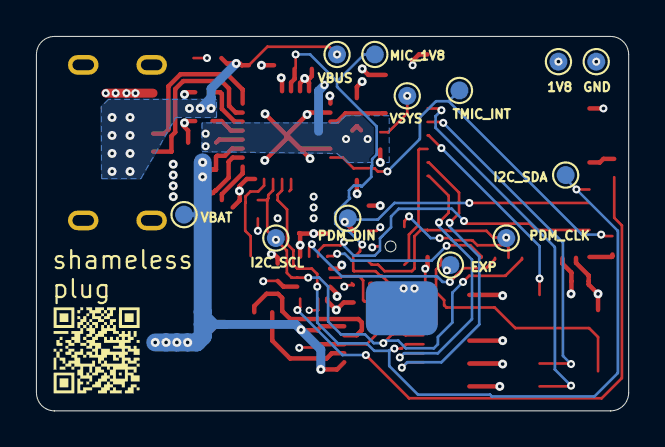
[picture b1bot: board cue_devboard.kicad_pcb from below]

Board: 4 copper layers, 32.9 x 20.8 mm, 51 parts (13 on the bottom side), 38 nets.

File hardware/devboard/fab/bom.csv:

Comment,Designator,Footprint,LCSC Part #,Manufacturer Part,Qty,Status,Sourcing,Notes
1uF,"C1,C4,C11,C12,C17,C19",C_0402_1005Metric,C52923,Samsung CL05A105KA5NQNC (1uF 25V X5R 0402),6,FIT,Basic,Load switch 1 output | U5 REG | U5 VDD | nPM1300 VBUSOUT must be decoupled
10uF,"C2,C5,C6,C18,C20,C21",C_0603_1608Metric,C96446,Samsung CL10A106MA8NRNC (10uF 25V X5R 0603),6,FIT,Basic,"PVDD, nPM1300 ref C2 (PVSS1 side) | nPM1300 ref C3 (PVSS2 side) | nPM1300 ref C4"
2.2uF,C3,C_0603_1608Metric,C23630,Samsung CL10A225KO8NNNC (2.2uF 16V X5R 0603),1,FIT,Basic,nPM1300 ref C6
4.7uF,C16,C_0402_1005Metric,C23733,Samsung CL05A475MP5NRNC (4.7uF 10V X5R 0402),1,FIT,Basic,U1 VDD bulk
100nF,"C8,C9,C10,C22",C_0402_1005Metric,C1525,Samsung CL05B104KO5NNNC (100nF 16V X7R 0402),4,FIT,Basic,"U3 VDD | U3 VDD_IO | U4 VDD, X7R, closest part to pin 7 | nPM1300 VDDIO pin 12, ref C13"
TVS 5V,D1,D_SOD-523,C82044,onsemi ESD5Z5.0T1G,1,FIT,Extended,Pad 1 = cathode to VBUS.
USB-C (power),J1,USB_C_Receptacle_GCT_USB4125-xx-x_6P_TopMnt_Horizontal,C5246813,GCT USB4125-GF-A-0190,1,FIT,Extended; 0 stock at JLCPCB 2026-10-05: pick any in-stock USB4125-GF-A variant (same footprint) or hand-solder,Charge-only USB-C. CC pull-downs (Rd) are inside the nPM1300.
BATT,J2,JST_PH_S2B-PH-SM4-TB_1x02-1MP_P2.00mm_Horizontal,C295747,JST S2B-PH-SM4-TB(LF)(SN),1,FIT,Extended,JST-PH for the Adafruit #1570 LiPo. Pin 1 = + (silk '+'). JST-PH battery leads are not standardised: meter the cell's plug before connecting; red must land on '+'.
LRA,J3,JST_SH_SM02B-SRSS-TB_1x02-1MP_P1.00mm_Horizontal,C160402,JST SM02B-SRSS-TB(LF)(SN),1,FIT,Extended,Coin LRA on a pigtail (Vybronics VG0832013D).
SWD,J4,PinHeader_2x05_P1.27mm_Vertical_SMD,C2932107,Samtec FTSH-105-01-L-DV-K-P-TR,1,FIT,Extended; check land pattern,ARM Cortex 10-pin debug pinout. VTref = 1V8.
2.2uH,L1,L_0805_2012Metric,C2049745,Murata DFE201210U-2R2M=P2,1,FIT,Extended,"BUCK1. Nordic ref: 2.2 uH, DCR < 400 mOhm. Confirm Murata land pattern vs 0805."
4.7k,"R1,R2",R_0402_1005Metric,C25900,UniOhm 0402WGF4701TCE,2,FIT,Basic,
47k,R3,R_0402_1005Metric,C25792,UniOhm 0402WGF4702TCE,1,FIT,Basic,VSET1 per Nordic reference circuit (BUCK1 1.8 V) - confirm in PS table
0R,R6,R_0402_1005Metric,C17168,UniOhm 0402WGF0000TCE,1,FIT,Basic,"Qvar series element, value TBC with ST guidance"
330R,"R7,R8",R_0402_1005Metric,C25104,UniOhm 0402WGF3300TCE,2,FIT,Basic,Cuff (BL54L15u) Ezurio Note 7: >=330 R series on P1.09-P1.12; kept so the boards match
10k NTC,RT1,R_0402_1005Metric,C77131,Murata NCP15XH103F03RC,1,FIT,Extended,10k 1% B25/50 3380 K (nPM1300 PS Table 11). Next to U2: with the cell on a lead it senses board temperature.
nPM1300,U2,QFN-32-1EP_5x5mm_P0.5mm_EP3.45x3.45mm,C7466043,Nordic NPM1300-QEAA-R,1,FIT,"Listed, out of stock: pre-order / global sourcing","I2C 0x6B. BUCK1=1V8 (VSET1), LS1 gates MIC_1V8. BUCK2 unused (nothing needs 3.0 V once J5 went): SW2 open, VSET2 to GND (= off at start-up), VOUT2 to VSYS per PS Configuration 2 (Fig. 57). BUCK1 and VSYS caps per PS v1.2.1 Configuration 1 (Table 38/39). LOADSW2 unused: LSIN2/LSOUT2 to GND per Fig. 57/58. NTC: 10k B3380 thermistor RT1 (Table 11); select it in ADCNTCRSEL. EP: KiCad 3.45 mm, inside the PS QFN32 E2/D2 range 3.40-3.60 mm."
LSM6DSV16BX,U3,LGA-14_3x2.5mm_P0.5mm_LayoutBorder3x4y,C5267394,ST LSM6DSV16BXTR,1,FIT,Extended; in stock at LCSC (2nd listing; C5381401 is the dead one),SA0=GND -> 0x6A. CS=1V8 -> I2C mode. Confirm ST land pattern matches KiCad LGA-14 3x2.5.
T5838,U4,TDK_T5838,C7230692,TDK MMICT5838-00-012,1,FIT,Extended,SELECT=GND -> right channel (data after the falling clock edge). Bottom port: 0.6 mm board hole (TDK: 0.5-1.0).
DRV2605L,U5,VSSOP-10_3x3mm_P0.5mm,C527464,TI DRV2605LDGSR,1,FIT,Extended,"I2C 0x5A, 1.8 V logic thresholds (VIH 1.3 V min). EN high before register writes. Supplied from VBAT (3.0-4.2 V): VSYS can approach VBUS while charging, above the 5.2 V max."

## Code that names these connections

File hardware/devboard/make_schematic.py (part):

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
# ------------------------------------------------------------------ pin names from datasheets
NPM1300 = {
    "1": "VOUT1", "2": "PVSS1", "3": "SW1", "4": "PVDD", "5": "SW2", "6": "PVSS2", "7": "GPIO0", "8": "GPIO1",
    "9": "GPIO2", "10": "GPIO3", "11": "GPIO4", "12": "VDDIO", "13": "SDA", "14": "SCL", "15": "SHPHLD",
    "16": "VSET2", "17": "VSET1", "18": "NTC", "19": "VBAT", "20": "VSYS", "21": "VBUS", "22": "VBUSOUT",
    "23": "CC1", "24": "CC2", "25": "LED0", "26": "LED1", "27": "LED2", "28": "LSIN1", "29": "LSOUT1",
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    wire(sw["2"], (sw["2"][0] - 2 * G, sw["2"][1]))  # ground clear of the button's name
    gnds.append(((sw["2"][0] - 2 * G, sw["2"][1]), 0))
    wire(u2["7"], (lx - 3 * G, row("7")))
    labels.append(("PMIC_INT", (lx - 3 * G, row("7")), 180))

    # ---- right: VSYS and PVDD to a rail of caps above
    vx = rx + 2 * G
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    wire(u2["4"], (vx, row("4")), (vx, rail), (rx + 17 * G, rail))
    for ref, dx in (("C4", 5), ("C5", 8), ("C20", 11), ("C21", 14)):
        hang(ref, rx + dx * G, rail)
    labels.append(("VSYS", (rx + 17 * G, rail), 0))

    # BUCK1: SW1 -> L1 -> 1V8; VOUT1, VDDIO and LSIN1 tie to it; output caps and I2C pull-ups hang off 1V8
    l1 = place("L1", 90, "1", rx + 3 * G, row("3"))
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    for ref, pad, dx in (("R2", "14", 21), ("R1", "13", 23)):
        r = place(ref, 180, "2", rx + dx * G, row("3"))  # pad 2 (1V8) up on the wire, pad 1 down to I2C
        wire(r["1"], (r["1"][0], row(pad)), u2[pad])
        labels.append(("I2C_SCL" if pad == "14" else "I2C_SDA", (rx + 10 * G, row(pad)), 0))

    # LOADSW1 -> MIC_1V8; LOADSW2 unused, both ends to GND (PS Fig. 57/58); exposed pad
    wire(u2["29"], (rx + 6 * G, row("29")))
    hang("C19", rx + 3 * G, row("29"))
    labels.append(("MIC_1V8", (rx + 6 * G, row("29")), 0))
    wire(u2["30"], (rx + G, row("30")), (rx + G, row("31")))
    wire(u2["31"], (rx + G, row("31")))
    gnds.append(((rx + G, row("31")), 0))
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
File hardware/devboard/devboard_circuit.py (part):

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    "8": "MIC_THSEL",      # P2.02
    "9": "HAPTIC_EN",      # P2.00 (output; P2 is fine for outputs)
    "10": "HAPTIC_TRIG",   # P2.01
    "14": "PDM_CLK",       # P1.03 clock pin (NFC2: configure as GPIO)
    "17": "BTN_USER",      # P0.00 user button (internal pull-up)
    "18": "EXP_P0_01",     # P0.01 spare to header
    "20": "IMU_INT1",      # P1.07 interrupt
    "21": "TDM_DIN",       # P1.06 -> I2S SDIN
    "22": "MIC_WAKE",      # P1.05 interrupt
    "23": "I2C_SCL",       # P1.04 clock pin
    "26": "1V8",           # VDD_nRF
    "28": "U1_PMIC_INT",   # P1.10 interrupt via R8 (cuff Note 7 resistor, kept so both boards match)
    "30": "TDM_BCLK",      # P1.08 clock pin -> I2S SCK
    "32": "PDM_DIN",       # P1.14
    "33": "I2C_SDA",       # P1.13
    "35": "U1_TDM_WCLK",   # P1.11 -> I2S LRCK via R7 (8-48 kHz)
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cap("C22", "100nF", "1V8", note="nPM1300 VDDIO pin 12, ref C13")
cap("C6", "10uF", "1V8", C0603); cap("C18", "10uF", "1V8", C0603)
cap("C8", "100nF", "1V8", note="U3 VDD"); cap("C9", "100nF", "1V8", note="U3 VDD_IO")
cap("C10", "100nF", "MIC_1V8", note="U4 VDD, X7R, closest part to pin 7")
cap("C19", "1uF", "MIC_1V8", note="Load switch 1 output")
cap("C11", "1uF", "VBAT", note="U5 VDD"); cap("C12", "1uF", "U5_REG", note="U5 REG")
cap("C16", "4.7uF", "1V8", note="U1 VDD bulk")
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    port = {"8": "P2.02", "9": "P2.00", "10": "P2.01", "14": "P1.03", "17": "P0.00", "18": "P0.01", "20": "P1.07",
            "21": "P1.06", "22": "P1.05", "23": "P1.04", "28": "P1.10", "29": "P1.09", "30": "P1.08", "32": "P1.14",
            "33": "P1.13", "34": "P1.12", "35": "P1.11"}
    # Port-1 pins marked "Clock pin" in the Ezurio BL54L15 pin-out table. LRCK (TDM_WCLK) does not need one.
    clock_pins = {"P1.03", "P1.04", "P1.08", "P1.11"}
    note7 = {"P1.09", "P1.10", "P1.11", "P1.12"}
    u1 = PARTS["U1"]["pins"]
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        net = net.removeprefix("U1_")
        if net in ("IMU_INT1", "MIC_WAKE", "PMIC_INT", "BTN_USER") and pp.startswith("P2."):
            problems.append(f"{net} on {pp}: port 2 cannot raise interrupts")
        if net in ("I2C_SCL", "PDM_CLK", "TDM_BCLK") and pp not in clock_pins:
            problems.append(f"{net} on {pp}: not a confirmed clock pin")
        if net in ("I2C_SDA", "PDM_DIN", "TDM_DIN") and not pp.startswith("P1."):
            problems.append(f"{net} on {pp}: serial data should stay on port 1")
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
